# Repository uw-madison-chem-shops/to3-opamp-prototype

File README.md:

# to3-opamp-prototype

...

## Repository

This is an open source hardware project licensed under the CERN Open Hardware Licence Version 2 - Permissive.
Please see the LICENSE file for the complete license.

This repository is being mirrored to several version control systems in an attempt to ensure maximum avaliability.

| name           | url                                                     |
| -------------- | ------------------------------------------------------- | 
| Chem (primary) | https://git.chem.wisc.edu/shop/fram-prototype           |
| GitHub         | https://github.com/uw-madison-chem-shops/fram-prototype | 
| GitLab         | https://gitlab.com/uw-madison-chem-shops/fram-prototype |

## PCB

This PCB was designed using KiCAD version 5.
Refer to `to-3-opamp-prototype.pdf` for schematic.
PCB images generated with [tracespace](https://github.com/tracespace/tracespace) follow.

## Changelog

### Revision A

#### Added
- initial design

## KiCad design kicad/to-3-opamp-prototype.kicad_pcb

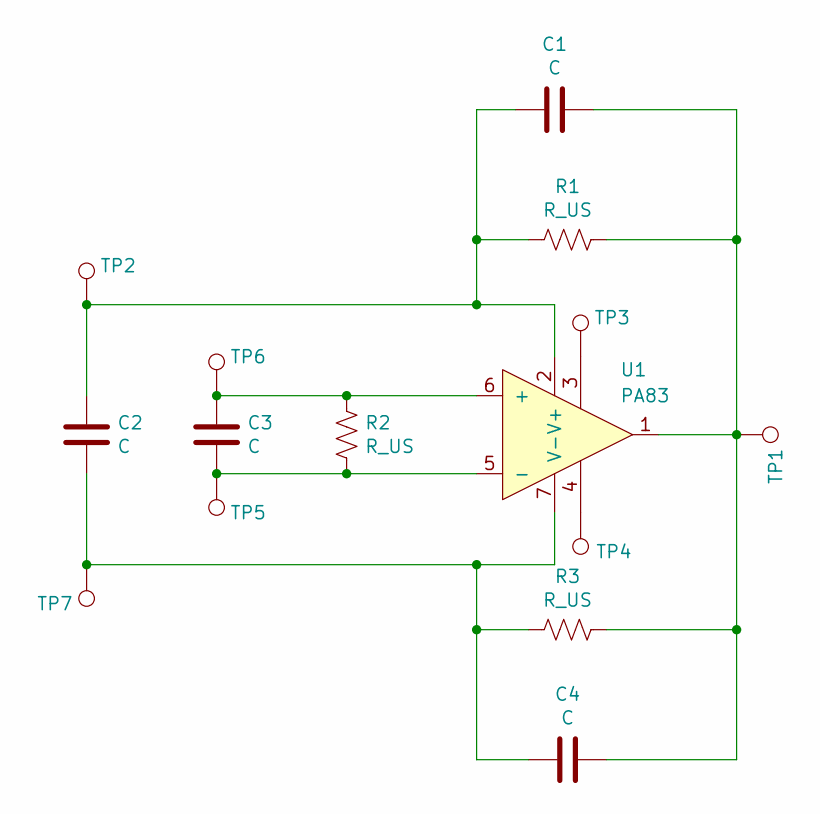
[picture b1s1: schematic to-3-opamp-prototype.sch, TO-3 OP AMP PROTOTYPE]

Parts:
C1, C2, C3, C4: C; R_Axial_DIN0207_L6.3mm_D2.5mm_P10.16mm_Horizontal
R1, R2, R3: R_US; R_Axial_DIN0207_L6.3mm_D2.5mm_P10.16mm_Horizontal
TP1, TP3, TP4, TP5, TP6, TP7: TestPoint; TestPoint_Plated_Hole_D2.0mm
TP2: +Vs; TestPoint_Plated_Hole_D2.0mm
U1: PA83; PA02

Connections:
unnamed: C1.1, C4.1, R1.1, R3.1, TP1.1, U1.1
unnamed: C1.2, C2.1, R1.2, TP2.1, U1.2 (V+)
unnamed: C2.2, C4.2, R3.2, TP7.1, U1.7 (V-)
unnamed: C3.1, R2.1, TP6.1, U1.6 (+)
unnamed: C3.2, R2.2, TP5.1, U1.5 (-)
unnamed: TP3.1, U1.3
unnamed: TP4.1, U1.4

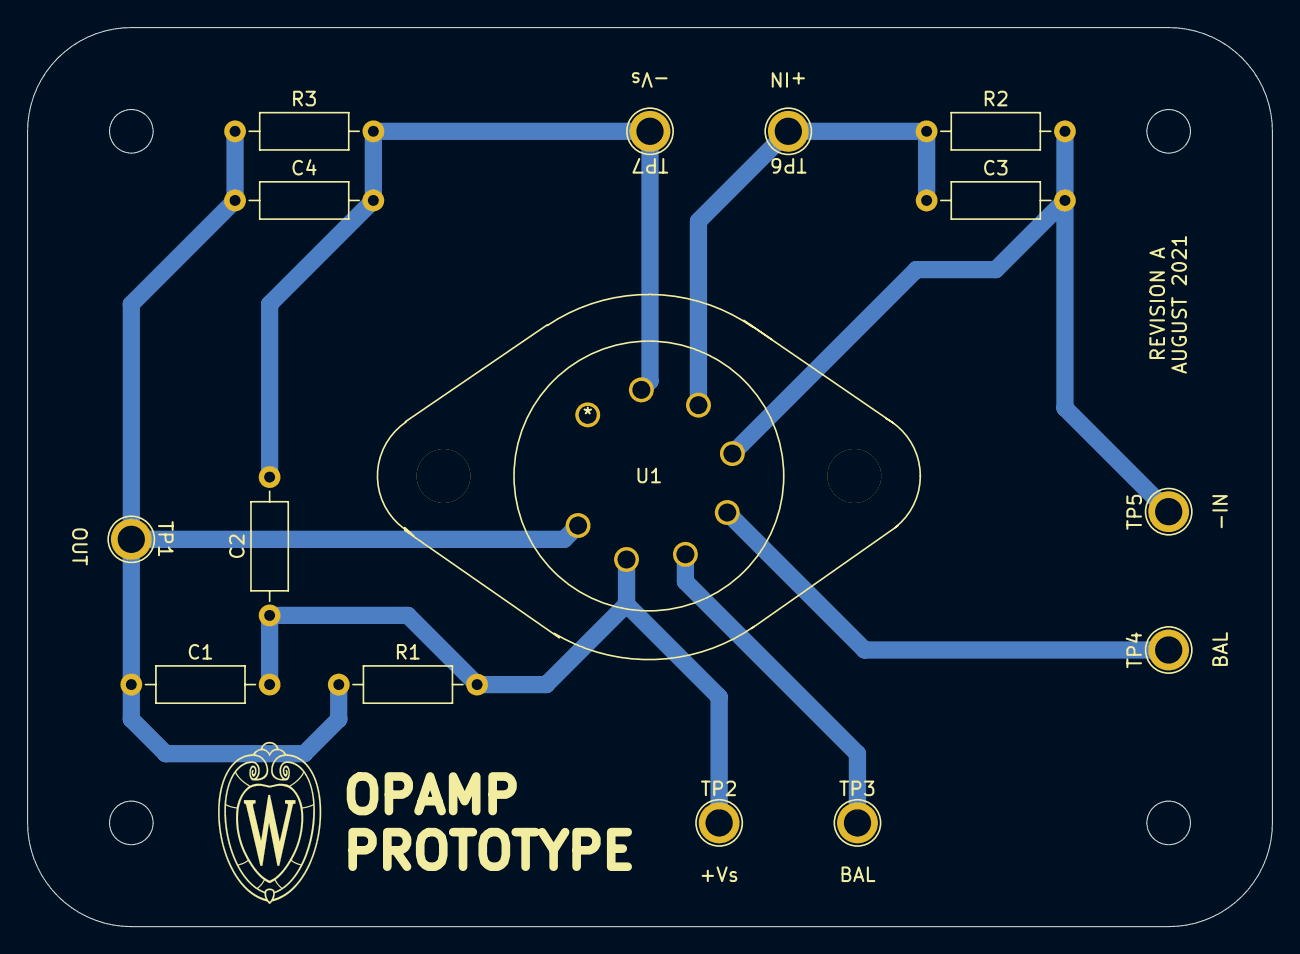
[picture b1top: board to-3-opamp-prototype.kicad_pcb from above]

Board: 2 copper layers, 91.4 x 66.0 mm, 15 parts (0 on the bottom side), 7 nets.

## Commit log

2021-08-06 revA

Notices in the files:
parts and their libraries:
Copyright 2021 Accelerated Designs. All rights reserved.
